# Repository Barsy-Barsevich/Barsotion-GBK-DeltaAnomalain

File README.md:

# Barsotion GBK DeltaAnomalain
Board computer for OKB Iva "Kilka" rocket, 2024

## Parameters
- Microcontroller: LGT8X328P
- Clock frequency: 32MHz
- Gyroscope: on-board MPU6050 (I2C)
- Barometer: external, 2x BMP388 (I2C)
- Memory: 8MB SPI NOR Flash

The clock frequency is 32 MHz provided by design, however before the flight 07.07.2024 we need to reduce it to 16 MHz, unless the computer was unstable in working.

## Software
- [DeltaAnomalain flight software](https://github.com/Barsy-Barsevich/KILKA_Soft)

## Continious progress
- [Previous version: Barsotion GBK GammaAnomalain](https://github.com/Barsy-Barsevich/Barsotion-GBK-GammaAnomalain)
- [Next version: Barsotion-EA (GBK EpsilonAnomalain](https://github.com/Barsy-Barsevich/Barsotion-EA)

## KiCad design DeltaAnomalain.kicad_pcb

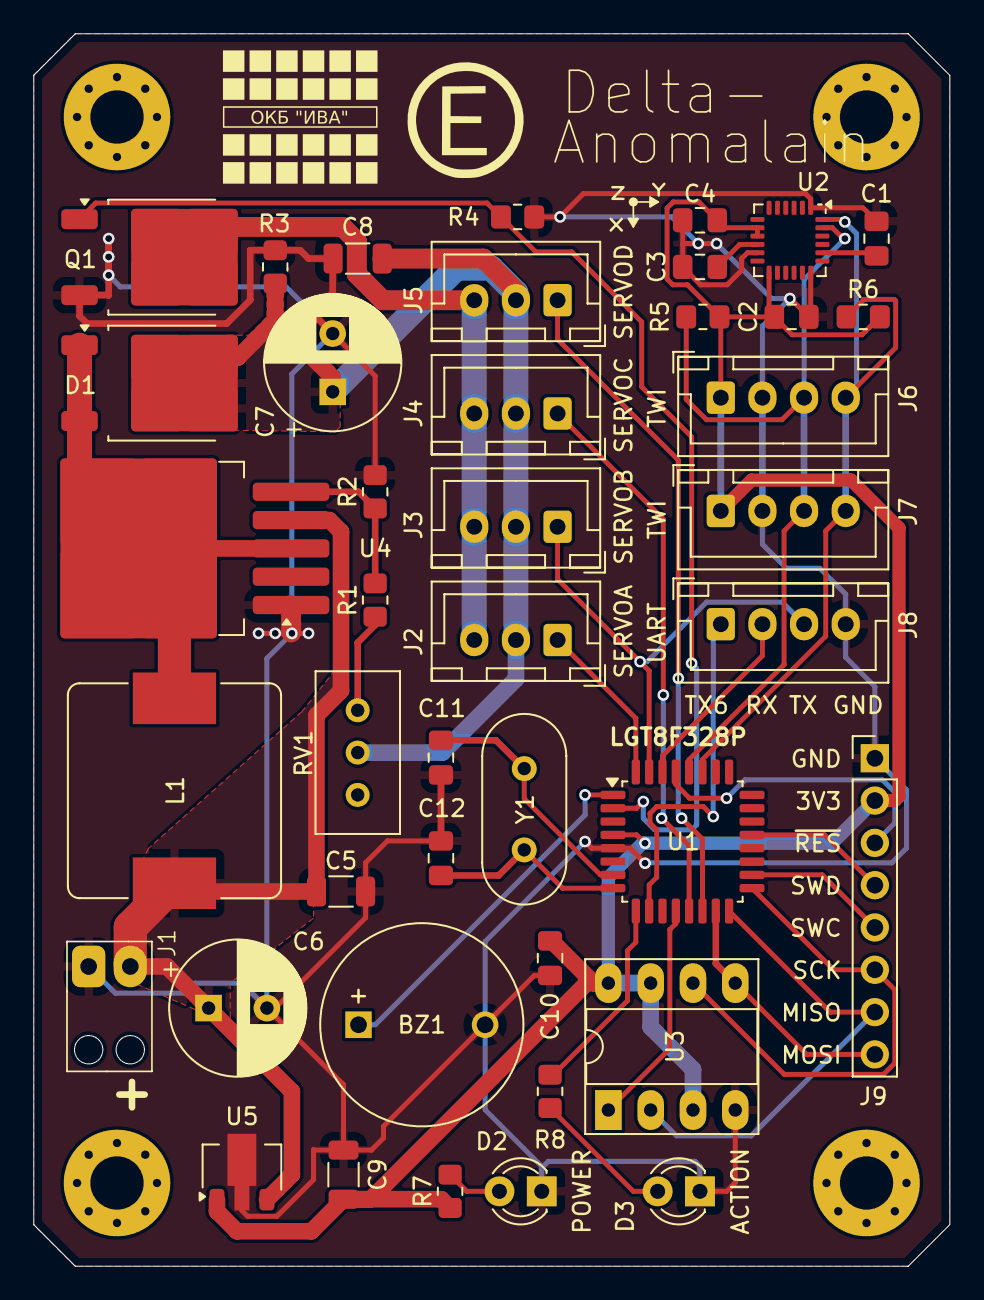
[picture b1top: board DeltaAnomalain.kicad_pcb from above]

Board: 2 copper layers, 55.0 x 74.0 mm, 46 parts (0 on the bottom side), 32 nets.

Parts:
BZ1: Buzzer; MagneticBuzzer_ProSignal_ABI-009-RC
C1: 2.2n; C_0805_2012Metric_Pad1.18x1.45mm_HandSolder
C2, C3, C4: 100n; C_0805_2012Metric_Pad1.18x1.45mm_HandSolder
C5, C8, C9: 1uF; C_1206_3216Metric
C6, C7: 470uF; CP_Radial_D8.0mm_P3.50mm
C10: 10nF; C_0805_2012Metric_Pad1.18x1.45mm_HandSolder
C11, C12: 22p; C_0805_2012Metric_Pad1.18x1.45mm_HandSolder
D1: MBRD1045; TO-252-2
D2: LED_Power; LED_D3.0mm
D3: LED_Active; LED_D3.0mm
H1, H2, H3, H4: MountingHole; MountingHole_3.2mm_M3_Pad_Via
J1: Power; Battery_3V7_Cable_solding_connctor
J2: SERVOA; JST_XH_B3B-XH-A_1x03_P2.50mm_Vertical
J3: SERVOB; JST_XH_B3B-XH-A_1x03_P2.50mm_Vertical
J4: SERVOC; JST_XH_B3B-XH-A_1x03_P2.50mm_Vertical
J5: SERVOD; JST_XH_B3B-XH-A_1x03_P2.50mm_Vertical
J6: BMP0; JST_XH_B4B-XH-A_1x04_P2.50mm_Vertical
J7: BMP1; JST_XH_B4B-XH-A_1x04_P2.50mm_Vertical
J8: UART; JST_XH_B4B-XH-A_1x04_P2.50mm_Vertical
J9: Prog; PinHeader_1x08_P2.54mm_Vertical
L1: 47uH; L_Bourns_SRP1245A
Q1: IRLR8726; TO-252-2
R1: 5.1k; R_0805_2012Metric_Pad1.20x1.40mm_HandSolder
R2: 1.8k; R_0805_2012Metric_Pad1.20x1.40mm_HandSolder
R3: 1k; R_0805_2012Metric_Pad1.20x1.40mm_HandSolder
R4, R5, R6, R7, R8: 10k; R_0805_2012Metric_Pad1.20x1.40mm_HandSolder
RV1: 2k; Potentiometer_Bourns_3296W_Vertical
U1: LGT8F328P; LQFP-32_7x7mm_P0.8mm
U2: MPU-6050; InvenSense_QFN-24_4x4mm_P0.5mm
U3: W25Q64FV; DIP-8_W7.62mm_Socket_LongPads
U4: XL6019; TO-263-5_TabPin3
U5: LD2981_SOT89; SOT-89-3
Y1: 32 MHz; Crystal_HC49-4H_Vertical

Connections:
3V3: C2.1, C4.1, C9.1, C10.1, J6.1, J7.1, J9.2, R5.2, R6.2, R7.1, U1.4 (VCC), U2.8 (VLOGIC), U2.9 (AD0), U2.13 (VDD), U3.3 (IO2), U3.7 (IO3), U3.8 (VCC), U5.1 (OUT)
3V7: C5.1, C6.1, J1.2, L1.1, U4.4 (VIN), U5.3 (IN)
BUZ: BZ1.1 (+), U1.1 (OC2B/INT1/PD3)
GND: BZ1.2 (-), C1.2, C2.2, C3.2, C4.2, C5.2, C6.2, C7.2, C8.2, C9.2, C10.2, C11.2, C12.2, D2.1 (K), D3.1 (K), J1.1, J6.2, J7.2, J8.4, J9.1, Q1.3 (S), R2.2, R3.2, R4.2, U1.5 (GND), U2.1 (CLKIN), U2.11 (FSYNC), U2.18 (GND), U3.4 (GND), U4.1 (GND), U5.2 (GND)
LED: R8.1, U1.9 (OC0B/T1/RXD/PD5)
MISO: J9.7, U1.16 (MISO/PB4), U3.2 (DO(IO1))
MOSI: J9.8, U1.15 (OC2A/MOSI/PB3), U3.5 (DI(IO0))
NRES: J9.3, U1.29 (RSTN/PC6)
unnamed: D2.2 (A), R7.2
unnamed: D3.2 (A), R8.2
unnamed: R1.1, RV1.1
unnamed: C1.1, U2.20 (CPOUT)
unnamed: C3.1, U2.10 (REGOUT)
unnamed: R1.2, R2.1, U4.5 (FB)
unnamed: D1.1 (A), D1.3 (A), L1.2, U4.3 (SW)
RXD: J8.2, U1.30 (RXD/PD0)
SCK: J9.6, U1.17 (ADC11/AC1P/SCK/PB5), U3.6 (CLK)
SCL: J6.3, J7.3, R5.1, U1.28 (SCL/ADC5/PC5), U2.23 (SCL)
SDA: J6.4, J7.4, R6.1, U1.27 (SDA/ADC4/PC4), U2.24 (SDA)
SERVOA: J2.1, U1.32 (OC3B/INT0/PD2)
SERVOB: J3.1, J8.3, U1.31 (OC3A/TXD/PD1)
SERVOC: J4.1, U1.13 (OC1A/PB1)
SERVOD: J5.1, U1.14 (SPSS/OC1B/PB2)
SERVOEN: Q1.1 (G), R4.1, U1.2 (XCK/T0/DA0/PD4)
SERVO_6V: C7.1, C8.1, D1.2 (K), J2.2, J3.2, J4.2, J5.2, R3.1, RV1.2
SERVO_GND: J2.3, J3.3, J4.3, J5.3, Q1.2 (D)
SWC: J9.5, U1.18 (APN4/SWC/PE0)
SWD: J9.4, U1.21 (SWD/PE2)
TXD6: J8.1, U1.10 (OC0A/AC0P/TXD/PD6)
W25NE: U1.12 (CLCO/ICP1/PB0), U3.1 (~CS)
XTAL0: C11.1, U1.7 (XTAL0/PB6), Y1.1
XTAL1: C12.1, U1.8 (XTAL1/PB7), Y1.2

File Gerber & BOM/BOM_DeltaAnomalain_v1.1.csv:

Reference,Value,Footprint,Qty,Description
BZ1,Buzzer,Buzzer_Beeper:MagneticBuzzer_ProSignal_ABI-009-RC,1,"Buzzer, polarized"
C1,2.2nF,Capacitor_SMD:C_0805_2012Metric_Pad1.18x1.45mm_HandSolder,1,Unpolarized capacitor
"C2,C3",100nF,Capacitor_SMD:C_0805_2012Metric_Pad1.18x1.45mm_HandSolder,2,Unpolarized capacitor
"C4,C10",10nF,Capacitor_SMD:C_0805_2012Metric_Pad1.18x1.45mm_HandSolder,2,Unpolarized capacitor
"C5,C8,C9",1uF,Capacitor_SMD:C_1206_3216Metric,3,Unpolarized capacitor
"C6,C7",470uF,Capacitor_THT:CP_Radial_D8.0mm_P3.50mm,2,Polarized capacitor
"C11,C12",22pF,Capacitor_SMD:C_0805_2012Metric_Pad1.18x1.45mm_HandSolder,2,Unpolarized capacitor
D1,MBRD1045,Package_TO_SOT_SMD:TO-252-2,1,"Schottky diode, anode on pins 1 and 3"
D2,LED_Power,LED_THT:LED_D3.0mm,1,Light emitting diode
D3,LED_Active,LED_THT:LED_D3.0mm,1,Light emitting diode
J1,Power,CustomConnectors:Battery_3V7_Cable_solding_connctor,1,"Generic connector, single row, 01x02, script generated"
J2,SERVOA,Connector_JST:JST_XH_B3B-XH-A_1x03_P2.50mm_Vertical,1,"Generic connector, single row, 01x03, script generated"
J3,SERVOB,Connector_JST:JST_XH_B3B-XH-A_1x03_P2.50mm_Vertical,1,"Generic connector, single row, 01x03, script generated"
J4,SERVOC,Connector_JST:JST_XH_B3B-XH-A_1x03_P2.50mm_Vertical,1,"Generic connector, single row, 01x03, script generated"
J5,SERVOD,Connector_JST:JST_XH_B3B-XH-A_1x03_P2.50mm_Vertical,1,"Generic connector, single row, 01x03, script generated"
J6,BMP0,Connector_JST:JST_XH_B4B-XH-A_1x04_P2.50mm_Vertical,1,"Generic connector, single row, 01x04, script generated"
J7,BMP1,Connector_JST:JST_XH_B4B-XH-A_1x04_P2.50mm_Vertical,1,"Generic connector, single row, 01x04, script generated"
J8,UART,Connector_JST:JST_XH_B4B-XH-A_1x04_P2.50mm_Vertical,1,"Generic connector, single row, 01x04, script generated"
J9,Prog,Connector_PinHeader_2.54mm:PinHeader_1x08_P2.54mm_Vertical,1,"Generic connector, single row, 01x08, script generated"
L1,47uH,Inductor_SMD:L_Bourns_SRP1245A,1,"Inductor with ferrite core, small symbol"
Q1,IRLR8726,Package_TO_SOT_SMD:TO-252-2,1,"35A Id, 60V Vds, N-Channel Power MOSFET, 18mOhm Ron, 19.3nC Qg (typ), TO252"
R1,5.1k,Resistor_SMD:R_0805_2012Metric_Pad1.20x1.40mm_HandSolder,1,Resistor
"R2,R3,R7,R8",1.8k,Resistor_SMD:R_0805_2012Metric_Pad1.20x1.40mm_HandSolder,4,Resistor
"R4,R5,R6",10k,Resistor_SMD:R_0805_2012Metric_Pad1.20x1.40mm_HandSolder,3,Resistor
RV1,2k,Potentiometer_THT:Potentiometer_Bourns_3296W_Vertical,1,Potentiometer
U1,LGT8F328P,Package_QFP:LQFP-32_7x7mm_P0.8mm,1,AVR-arch LGTX8-core 32MHz 8-bit MCU
U2,MPU6050,Sensor_Motion:InvenSense_QFN-24_4x4mm_P0.5mm,1,"InvenSense 6-Axis Motion Sensor, Gyroscope, Accelerometer, I2C"
U3,W25Q64FV,Package_DIP:DIP-8_W7.62mm_Socket_LongPads,1,"16Mb Serial Flash Memory, Standard/Dual/Quad SPI, SOIC-8"
U4,XL6019,Package_TO_SOT_SMD:TO-263-5_TabPin3,1,DC-DC 5A 36V Impulse PULLUP converter
U5,LD2981_SOT89,Package_TO_SOT_SMD:SOT-89-3,1,"Positive 100mA 30V Linear Regulator, Fixed Output 3.3V, SOT-89"
Y1,32 MHz,Crystal:Crystal_HC49-4H_Vertical,1,Two pin crystal

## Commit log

2025-03-06 gitignore add
2025-03-06 Create LICENSE
2025-03-10 readme update
